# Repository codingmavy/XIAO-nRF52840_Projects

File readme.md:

# BLE Analyzer (Zephyr, nRF52840)

A BLE advertisement scanner running entirely on hardware and firmware. It scans nearby devices and prints every captured packet over a USB serial (COM) port. No host software is needed; any serial terminal can read the output.

**Status:** in development.

**Responsible use:** passive scanning only, on your own devices or with permission.

## Features

- Passive scan of BLE advertisements (no connections, no transmission)
- Per packet: timestamp, device address, address type, advertisement type, RSSI, and raw advertising data
- One line of output per packet over USB serial
- Duplicates are not filtered, so repeated packets give RSSI samples

## Limitations

- Uses Zephyr's host scanner, so it cannot see CRC-failed packets or the channel a packet arrived on, and it cannot follow connections
- Cannot read encrypted traffic

## Hardware

- Seeed XIAO nRF52840 (SMD) mounted on a custom PCB, programmed and debugged over SWD
- 2x nRF24L01 modules on the same PCB (wired, not used by the current firmware)
- ST-Link probe for flashing

### nRF52840

The nRF52840 does all the work in this version: its BLE radio scans, the CPU timestamps and formats each packet, and the USB port carries the output to the PC.

### nRF24L01 modules

The two modules are wired but unused for now. The nRF24L01 uses its own packet format and cannot properly receive BLE traffic, so it takes no part in the BLE scanner. Planned uses are listed under Upcoming.

Both modules share one SPI bus. Each has its own CSN, CE, and IRQ line, which uses 9 GPIO pins in total.

#### Schematic

#### Pin map (XIAO nRF52840 SMD)

| XIAO pin | Signal | Goes to |
|---|---|---|
| D0 | CE_1 | Radio 1, CE |
| D1 | CSN_1 | Radio 1, CSN |
| D2 | CE_2 | Radio 2, CE |
| D3 | CSN_2 | Radio 2, CSN |
| D4 | IRQ_1 | Radio 1, IRQ |
| D5 | IRQ_2 | Radio 2, IRQ |
| D6 | not connected | Free |
| D7 | not connected | Free |
| D8 | SCK | Both radios, SCK |
| D9 | MISO | Both radios, MISO |
| D10 | MOSI | Both radios, MOSI |
| 3V3_OUT | +3.3 V | Both radios, VCC |
| GND | GND | Both radios, GND |
| VBUS | not connected | Unused |

Notes:
- 3.3 V only, never 5 V
- Each module has a 10 uF capacitor on VCC, placed close to the pins
- Keep SPI wires short, since the bus is shared

## What the firmware does

1. Initializes the Bluetooth stack and the USB serial port
2. Runs a continuous passive scan on the advertising channels
3. For each advertisement, reads the address, address type, advertisement type, RSSI, and raw advertising data
4. Attaches an uptime timestamp
5. Prints one line per packet to the USB serial port
6. Prints an error line if Bluetooth or scanning fails to start
7. Never connects to or transmits to other devices

## Output format

One comma-separated line per packet:

```
ADV,<uptime_ms>,<address>,<adv_type>,<rssi_dbm>,<data_length>,<data_hex>
```

Status and error lines start with `INFO` or `ERR`.

## Build and flash

Board target: `xiao_ble/nrf52840`. Flashing uses an ST-Link over SWD through OpenOCD.

Build:

```bash
west build -b xiao_ble/nrf52840
```

Pristine build (wipes the build folder first, use after changing the board, overlay, or Kconfig):

```bash
west build -b xiao_ble/nrf52840 -p always
```

Flash over SWD with ST-Link:

```bash
west flash --cmd-pre-init "source [find interface/stlink.cfg]" \
           --cmd-pre-init "transport select swd" \
           --cmd-pre-init "source [find target/nordic/nrf52.cfg]"
```

Wiring for flashing: connect the ST-Link's SWDIO, SWCLK, and GND to the board's SWD pads, and make sure the board is powered.

Troubleshooting:
- If `west` picks the wrong runner, add `-r openocd` to the flash command, and check the available runners with `west flash --context`
- If OpenOCD cannot connect, check the SWD wiring, the ST-Link connection, and that the board has power
- If the chip is locked, run a recover erase first. This wipes the whole chip, which also removes the UF2 bootloader, so the UF2 fallback below will stop working until you reinstall the bootloader
- Fallback without a probe: double-tap the reset button to enter the UF2 bootloader, then flash the UF2 file with `west flash -r uf2`

## Viewing the output

Plug the board into the PC over USB, open the COM port in any serial terminal, and the packet lines appear as the scan runs.

## Upcoming

Firmware:
- Shell for changing scan interval and window
- Per-device filtering by address or RSSI
- Record counter so lost packets can be detected
- On-device RSSI filtering
- Advertising data decoding (flags, name, TX power, manufacturer data, iBeacon, Eddystone)
- Private address rotation detection

nRF24L01 radios:
- Register read and write test on both modules
- Loopback test between the two radios
- 2.4 GHz occupancy scan, with each radio sweeping half the band
- Wireless data link between two boards

Host tools:
- Host reader with CSV logging
- Distance estimation from RSSI with calibration
- PCAP export for Wireshark
- Live dashboard

Project quality:
- Unit tests and CI
- Measured results table
- Raw-radio sniffer with connection following
- ESP32 port
- Angle of arrival

## License

Choose MIT or Apache-2.0 and credit any code you reuse.

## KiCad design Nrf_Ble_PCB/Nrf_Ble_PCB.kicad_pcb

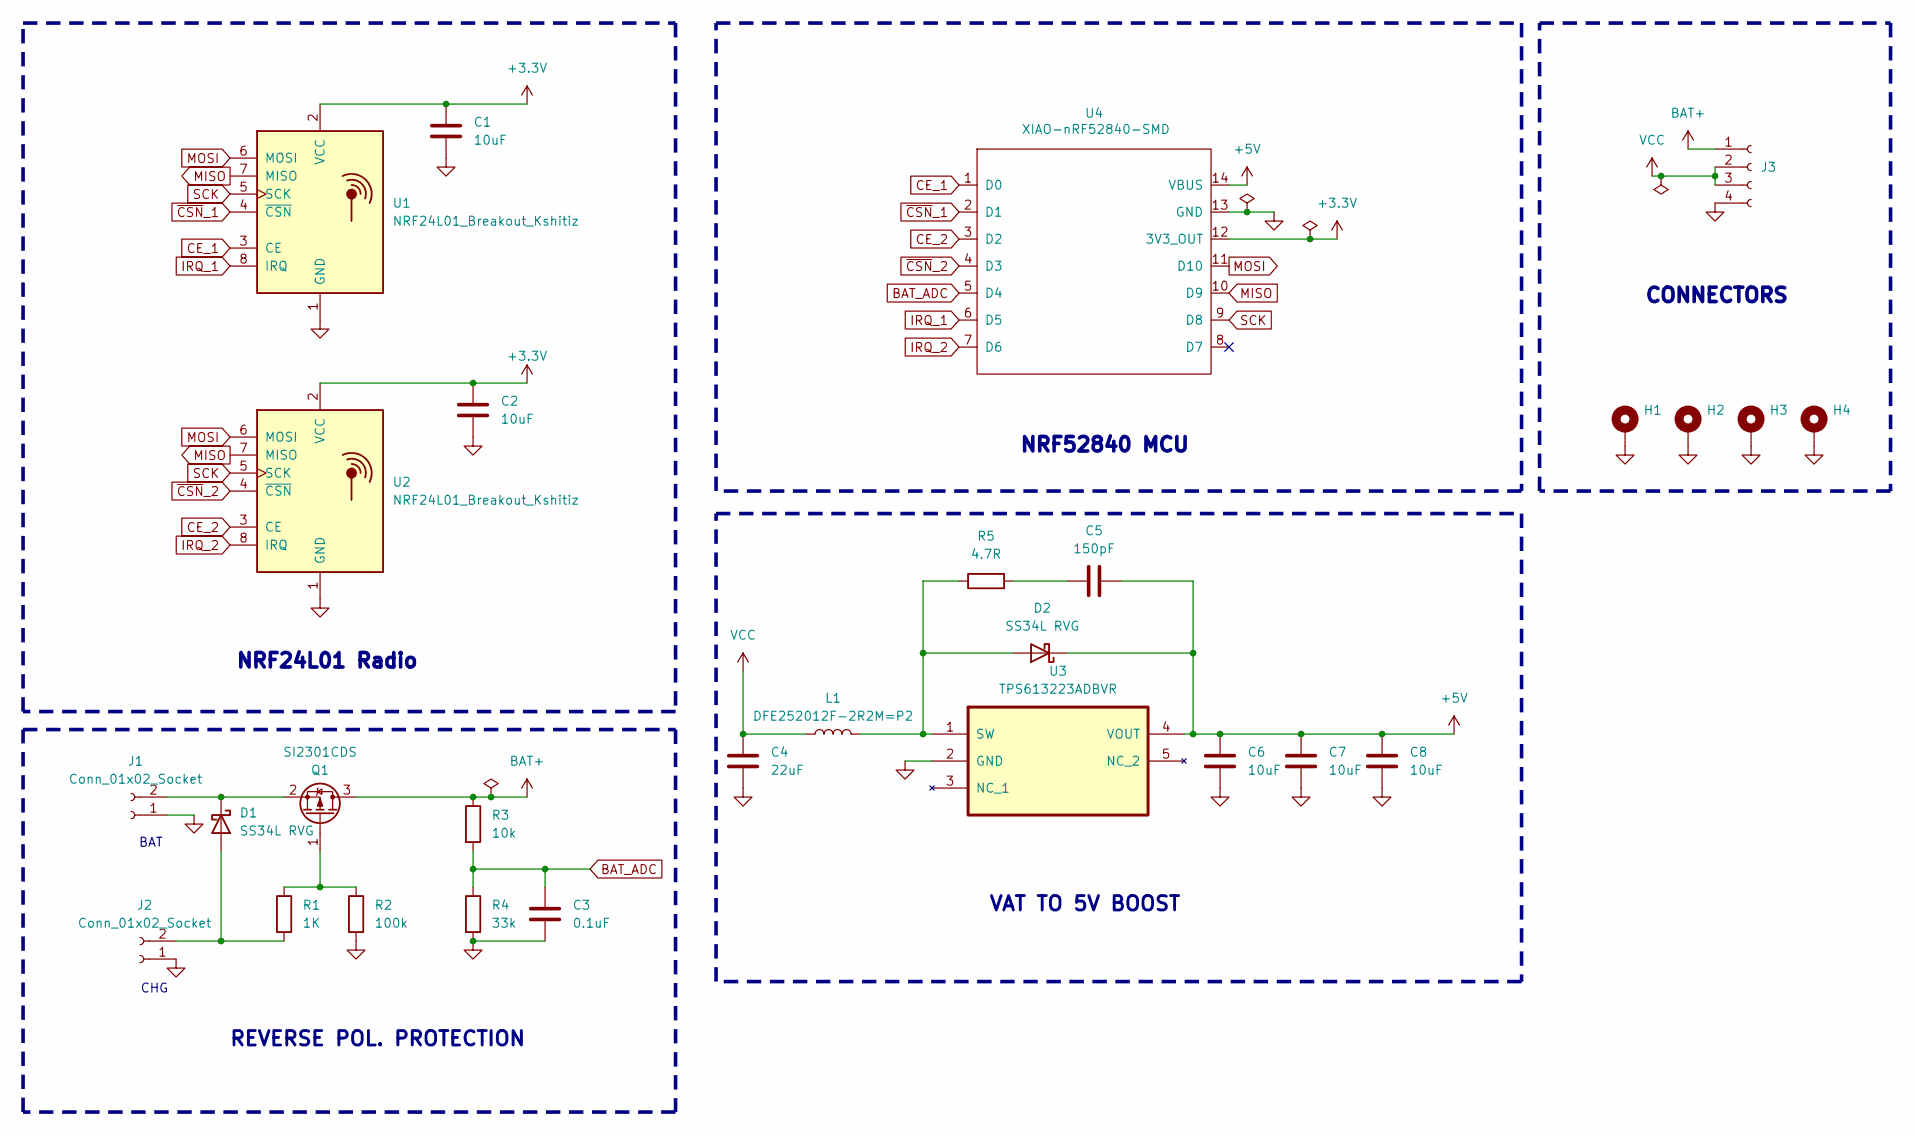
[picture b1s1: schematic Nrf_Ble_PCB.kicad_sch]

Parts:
C1, C2, C6, C7, C8: 10uF; C_0805_2012Metric
C3: 0.1uF; C_0805_2012Metric
C4: 22uF; C_0805_2012Metric
C5: 150pF; C_0805_2012Metric
D1, D2: SS34L RVG; D_SMA
H1, H2, H3, H4: MountingHole_Pad; MountingHole_3.2mm_M3_Pad_Via
J1, J2: Conn_01x02_Socket; JST_XH_B2B-XH-A_1x02_P2.50mm_Vertical
J3: Conn_01x04_Socket; JST_XH_B4B-XH-A_1x04_P2.50mm_Vertical
L1: DFE252012F-2R2M=P2; L_1008_2520Metric
Q1: SI2301CDS; SOT-23
R1: 1K; R_0805_2012Metric
R2: 100k; R_0805_2012Metric
R3: 10k; R_1210_3225Metric
R4: 33k; R_0805_2012Metric
R5: 4.7R; R_0603_1608Metric
U1, U2: NRF24L01_Breakout_Kshitiz; nRF24L01_Breakout_Centered
U3: TPS613223ADBVR; TPS613223ADBVR_new
U4: XIAO-nRF52840-SMD; XIAO-nRF52840-DIP_silkscreen_cut

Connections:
+3.3V: C1.1, C2.1, U1.2 (VCC), U2.2 (VCC), U4.12 (3V3_OUT)
+5V: C5.2, C6.1, C7.1, C8.1, D2.1 (K), U3.4 (VOUT), U4.14 (VBUS)
BAT+: J3.1, Q1.3 (D), R3.1
BAT_ADC: C3.1, R3.2, R4.1, U4.5 (D4)
CE_1: U1.3 (CE), U4.1 (D0)
CE_2: U2.3 (CE), U4.3 (D2)
GND: C1.2, C2.2, C3.2, C4.2, C6.2, C7.2, C8.2, H1.1 (1_1), H2.1 (1_1), H3.1 (1_1), H4.1 (1_1), J1.1, J2.1, J3.4, R2.2, R4.2, U1.1 (GND), U2.1 (GND), U3.2 (GND), U4.13 (GND)
IRQ_1: U1.8 (IRQ), U4.6 (D5)
IRQ_2: U2.8 (IRQ), U4.7 (D6)
MISO: U1.7 (MISO), U2.7 (MISO), U4.10 (D9)
MOSI: U1.6 (MOSI), U2.6 (MOSI), U4.11 (D10)
unnamed: C5.1, R5.2
unnamed: D1.2 (A), J2.2, R1.2
unnamed: D1.1 (K), J1.2, Q1.2 (S)
unnamed: D2.2 (A), L1.2, R5.1, U3.1 (SW)
unnamed: Q1.1 (G), R1.1, R2.1
SCK: U1.5 (SCK), U2.5 (SCK), U4.9 (D8)
VCC: C4.1, J3.2, J3.3, L1.1
~CSN_1: U1.4 (~CSN), U4.2 (D1)
~CSN_2: U2.4 (~CSN), U4.4 (D3)

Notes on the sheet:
REVERSE POL. PROTECTION
CONNECTORS
NRF24L01 Radio
NRF52840 MCU
BAT
VAT TO 5V BOOST
CHG

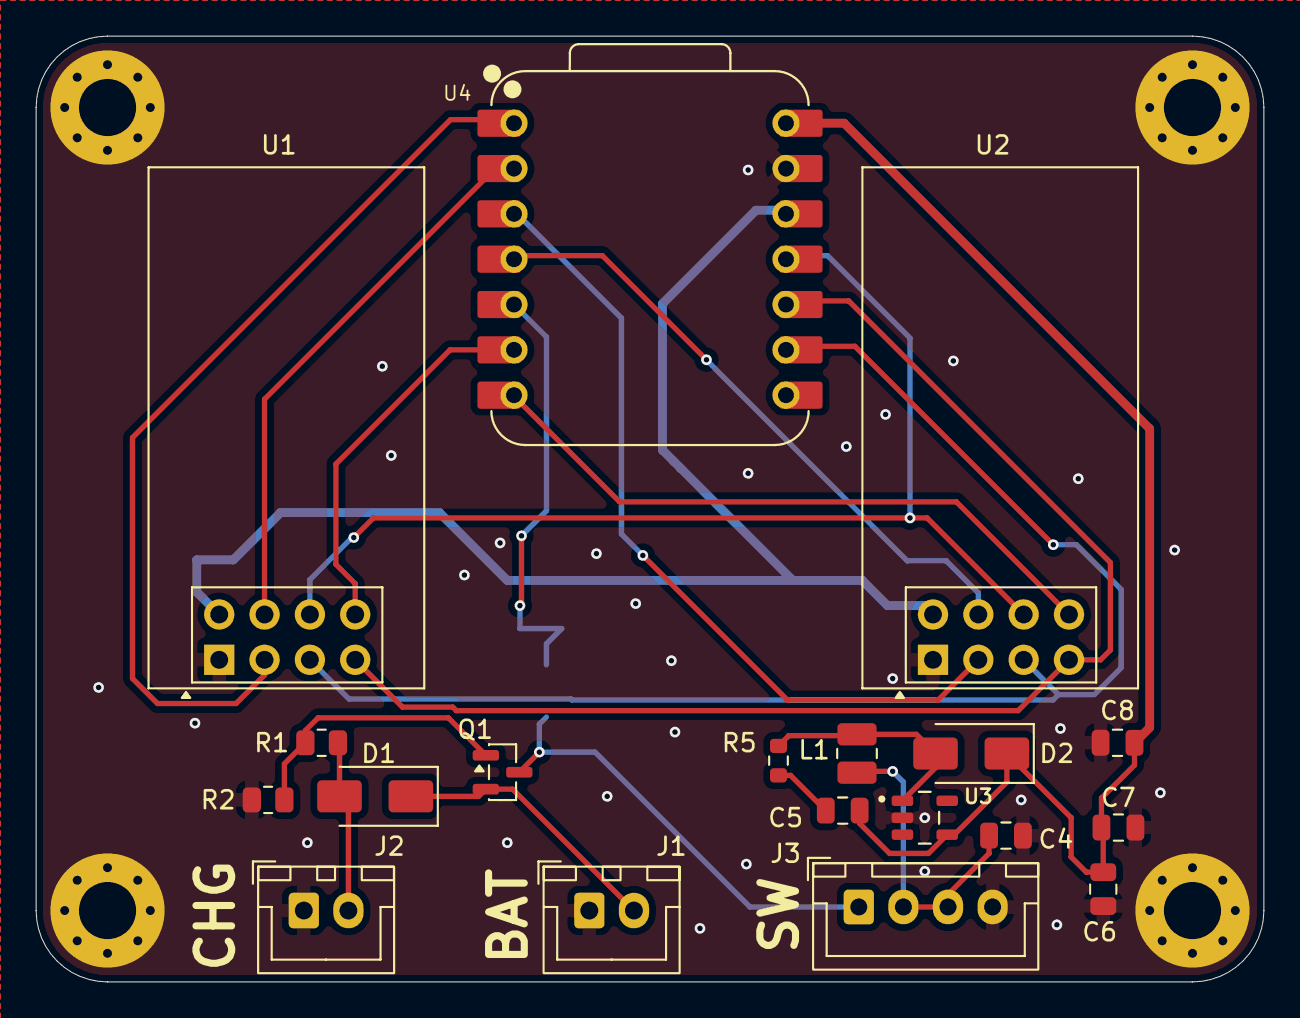
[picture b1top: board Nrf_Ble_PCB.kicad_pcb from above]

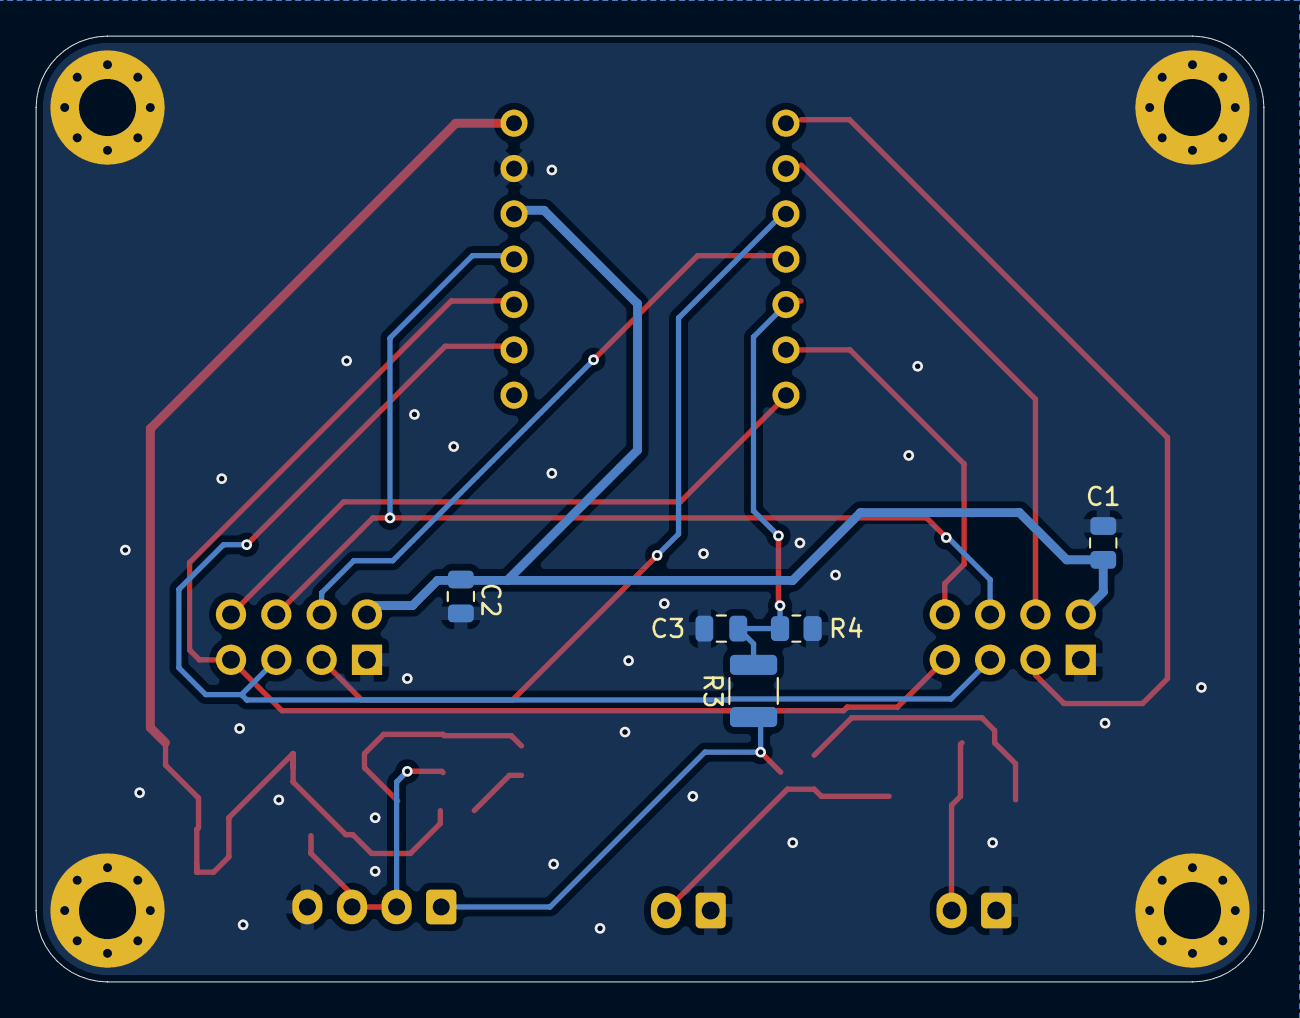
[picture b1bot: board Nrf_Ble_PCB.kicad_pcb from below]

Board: 2 copper layers, 68.8 x 53.0 mm, 28 parts (5 on the bottom side), 20 nets.
